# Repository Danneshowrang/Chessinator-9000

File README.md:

# Chessinator-9000
A smart open source folding chessboard. Future expansions planned with electromagnetic gantry.

# About
This board utilizes a network of hall sensors to track and log moves. Made up of 2 adjacent PCBs and designed to be foldable for improved portability. Future plans include a supplementary electromagnetic gantry and API connection to Lichess and Chess.com. Currently configured to project move and take a crowdvote for Open Sauce.

# Pictures

# CAD
Link to Onshape: https://cad.onshape.com/documents/2e4e2dec579cd54b02eea52a/w/9b3b1f51bd0c7211bdccebd8/e/a09db839a12e81c960572c26?renderMode=0&uiState=6a51f7b7bcb9fa1e94df709e

# Bill Of Materials

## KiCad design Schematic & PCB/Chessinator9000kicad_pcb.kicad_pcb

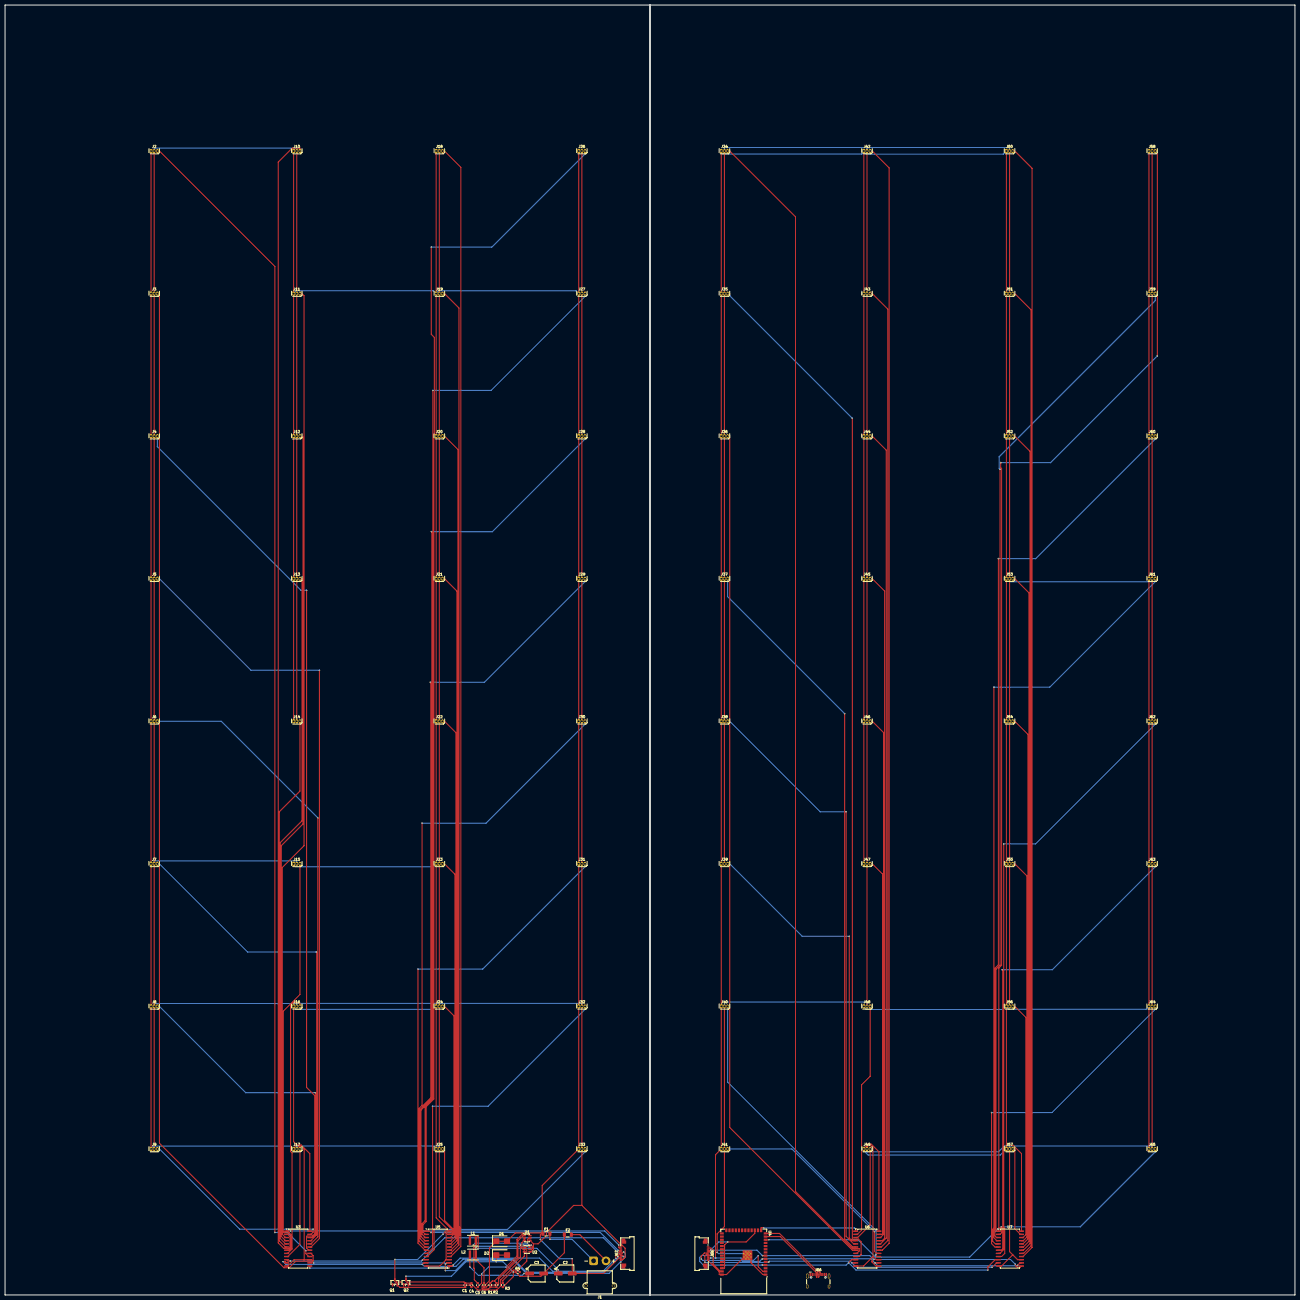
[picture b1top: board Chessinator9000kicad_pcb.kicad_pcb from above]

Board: 2 copper layers, 517.1 x 517.1 mm, 93 parts (0 on the bottom side), 91 nets.

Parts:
C1, C4, C5, C6: C; C_0603_1608Metric
C2, C3: C_Polarized; CP_Elec_6.3x5.4
D1, D2: D_TVS; D_SMB
F1, F2: Fuse; Fuse_1206_3216Metric
J1: Conn_01x02; AMASS_XT30PW-M_1x02_P2.50mm_Horizontal
J2, J3, J4, J5, J6, J7, J8, J9, J10, J11, J12, J13, J14, J15, J16, J17, J18, J19, J20, J21, J22, J23, J24, J25, J26, J27, J28, J29, J30, J31, J32, J33, J34, J35, J36, J37, J38, J39, J40, J41, J42, J43, J44, J45, J46, J47, J48, J49, J50, J51, J52, J53, J54, J55, J56, J57, J58, J59, J60, J61, J62, J63, J64, J65: Conn_01x03; TO-92S
J66: USB_C_Receptacle_USB2.0_16P; USB_C_Receptacle_HCTL_HC-TYPE-C-16P-01A
J67, J68: Conn_02x06_Odd_Even; Amphenol_F32Q-1A7x1-11012_1x12-1MP_P0.5mm_Horizontal
L1, L2: L; L_Coilcraft_XxL4020
Q1, Q2: PMOS; SOT-23
R1, R2, R3, R4: R; R_0603_1608Metric
U1: AP63203WU; TSOT-23-6
U2: AP63201WU; TSOT-23-6
U3, U5, U6, U7: CD74HC4067M; SOIC-24W_7.5x15.4mm_P1.27mm
U4: ESP32-S3-WROOM-1

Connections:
+3V3: C2.2, D1.1 (A1), D1.2 (A2), F1.1, J2.1 (VCC), J3.1 (VCC), J4.1 (VCC), J5.1 (VCC), J6.1 (VCC), J7.1 (VCC), J8.1 (VCC), J9.1 (VCC), J10.1 (VCC), J11.1 (VCC), J12.1 (VCC), J13.1 (VCC), J14.1 (VCC), J15.1 (VCC), J16.1 (VCC), J17.1 (VCC), J18.1 (VCC), J19.1 (VCC), J20.1 (VCC), J21.1 (VCC), J22.1 (VCC), J23.1 (VCC), J24.1 (VCC), J25.1 (VCC), J26.1 (VCC), J27.1 (VCC), J28.1 (VCC), J29.1 (VCC), J30.1 (VCC), J31.1 (VCC), J32.1 (VCC), J33.1 (VCC), J34.1 (VCC), J35.1 (VCC), J36.1 (VCC), J37.1 (VCC), J38.1 (VCC), J39.1 (VCC), J40.1 (VCC), J41.1 (VCC), J42.1 (VCC), J43.1 (VCC), J44.1 (VCC), J45.1 (VCC), J46.1 (VCC), J47.1 (VCC), J48.1 (VCC), J49.1 (VCC), J50.1 (VCC), J51.1 (VCC), J52.1 (VCC), J53.1 (VCC), J54.1 (VCC), J55.1 (VCC), J56.1 (VCC), J57.1 (VCC), J58.1 (VCC), J59.1 (VCC), J60.1 (VCC), J61.1 (VCC), J62.1 (VCC), J63.1 (VCC), J64.1 (VCC), J65.1 (VCC), J67.3, J67.4, J68.9, J68.10, Q1.3 (S), R1.1, R2.1, U3.24 (VCC), U4.2 (3V3), U5.24 (VCC), U6.24 (VCC), U7.24 (VCC)
+5V: C3.2, D2.1 (A1), D2.2 (A2), F2.1, Q2.3 (S), R3.1, R4.1
/Untitled Sheet/MUX3_COM: J67.9, J68.4, U4.17 (IO9), U4.38 (IO2), U5.1 (COM)
/Untitled Sheet/MUX4_COM: J67.10, J68.3
/Untitled Sheet/MUX_COM_EXTRA: J67.11, J68.2, U3.1 (COM), U4.39 (IO1)
/Untitled Sheet/MUX_S0: J67.5, J68.8, U3.10 (S0), U4.4 (IO4), U5.10 (S0), U6.10 (S0), U7.10 (S0)
/Untitled Sheet/MUX_S1: J67.6, J68.7, U3.11 (S1), U4.5 (IO5), U5.11 (S1), U6.11 (S1), U7.11 (S1)
/Untitled Sheet/MUX_S2: J67.7, J68.6, U3.14 (S2), U4.6 (IO6), U5.14 (S2), U6.14 (S2), U7.14 (S2)
/Untitled Sheet/MUX_S3: J67.8, J68.5, U3.13 (S3), U4.7 (IO7), U5.13 (S3), U6.13 (S3), U7.13 (S3)
GND: J2.2 (GND), J3.2 (GND), J4.2 (GND), J5.2 (GND), J6.2 (GND), J7.2 (GND), J8.2 (GND), J9.2 (GND), J10.2 (GND), J11.2 (GND), J12.2 (GND), J13.2 (GND), J14.2 (GND), J15.2 (GND), J16.2 (GND), J17.2 (GND), J18.2 (GND), J19.2 (GND), J20.2 (GND), J21.2 (GND), J22.2 (GND), J23.2 (GND), J24.2 (GND), J25.2 (GND), J26.2 (GND), J27.2 (GND), J28.2 (GND), J29.2 (GND), J30.2 (GND), J31.2 (GND), J32.2 (GND), J33.2 (GND), J34.2 (GND), J35.2 (GND), J36.2 (GND), J37.2 (GND), J38.2 (GND), J39.2 (GND), J40.2 (GND), J41.2 (GND), J42.2 (GND), J43.2 (GND), J44.2 (GND), J45.2 (GND), J46.2 (GND), J47.2 (GND), J48.2 (GND), J49.2 (GND), J50.2 (GND), J51.2 (GND), J52.2 (GND), J53.2 (GND), J54.2 (GND), J55.2 (GND), J56.2 (GND), J57.2 (GND), J58.2 (GND), J59.2 (GND), J60.2 (GND), J61.2 (GND), J62.2 (GND), J63.2 (GND), J64.2 (GND), J65.2 (GND), J67.1, J67.2, J68.11, J68.12, U1.4 (GND), U2.4 (GND), U3.12 (GND), U3.15 (~E), U4.1 (GND), U4.40 (GND), U4.41 (GND), U5.12 (GND), U5.15 (~E), U6.12 (GND), U6.15 (~E), U7.12 (GND), U7.15 (~E)
unnamed: C2.1, L1.1
unnamed: C3.1, L2.1
unnamed: F1.2, J1.1
unnamed: F2.2, J1.2
unnamed: J2.3 (PIT), U3.16 (I15)
unnamed: J3.3 (PIT), U3.17 (I14)
unnamed: J4.3 (PIT), U3.18 (I13)
unnamed: J5.3 (PIT), U3.19 (I12)
unnamed: J6.3 (PIT), U3.20 (I11)
unnamed: J7.3 (PIT), U3.21 (I10)
unnamed: J8.3 (PIT), U3.22 (I9)
unnamed: J9.3 (PIT), U3.23 (I8)
unnamed: J10.3 (PIT), U3.2 (I7)
unnamed: J11.3 (PIT), U3.3 (I6)
unnamed: J12.3 (PIT), U3.4 (I5)
unnamed: J13.3 (PIT), U3.5 (I4)
unnamed: J14.3 (PIT), U3.6 (I3)
unnamed: J15.3 (PIT), U3.7 (I2)
unnamed: J16.3 (PIT), U3.8 (I1)
unnamed: J17.3 (PIT), U3.9 (I0)
unnamed: J18.3 (PIT), U5.16 (I15)
unnamed: J19.3 (PIT), U5.17 (I14)
unnamed: J20.3 (PIT), U5.18 (I13)
unnamed: J21.3 (PIT), U5.19 (I12)
unnamed: J22.3 (PIT), U5.20 (I11)
unnamed: J23.3 (PIT), U5.21 (I10)
unnamed: J24.3 (PIT), U5.22 (I9)
unnamed: J25.3 (PIT), U5.23 (I8)
unnamed: J26.3 (PIT), U5.2 (I7)
unnamed: J27.3 (PIT), U5.3 (I6)
unnamed: J28.3 (PIT), U5.4 (I5)
unnamed: J29.3 (PIT), U5.5 (I4)
unnamed: J30.3 (PIT), U5.6 (I3)
unnamed: J31.3 (PIT), U5.7 (I2)
unnamed: J32.3 (PIT), U5.8 (I1)
unnamed: J33.3 (PIT), U5.9 (I0)
unnamed: J34.3 (PIT), U6.8 (I1)
unnamed: J35.3 (PIT), U6.9 (I0)
unnamed: J36.3 (PIT), U6.7 (I2)
unnamed: J37.3 (PIT), U6.6 (I3)
unnamed: J38.3 (PIT), U6.5 (I4)
unnamed: J39.3 (PIT), U6.4 (I5)
unnamed: J40.3 (PIT), U6.16 (I15)
unnamed: J41.3 (PIT), U6.17 (I14)
unnamed: J42.3 (PIT), U6.18 (I13)
unnamed: J43.3 (PIT), U6.19 (I12)
unnamed: J44.3 (PIT), U6.20 (I11)
unnamed: J45.3 (PIT), U6.21 (I10)
unnamed: J46.3 (PIT), U6.22 (I9)
unnamed: J47.3 (PIT), U6.23 (I8)
unnamed: J48.3 (PIT), U6.2 (I7)
unnamed: J49.3 (PIT), U6.3 (I6)
unnamed: J50.3 (PIT), U7.16 (I15)
unnamed: J51.3 (PIT), U7.17 (I14)
unnamed: J52.3 (PIT), U7.18 (I13)
unnamed: J53.3 (PIT), U7.19 (I12)
unnamed: J54.3 (PIT), U7.20 (I11)
unnamed: J55.3 (PIT), U7.21 (I10)
unnamed: J56.3 (PIT), U7.22 (I9)
unnamed: J57.3 (PIT), U7.23 (I8)
unnamed: J58.3 (PIT), U7.2 (I7)
unnamed: J59.3 (PIT), U7.3 (I6)
unnamed: J60.3 (PIT), U7.4 (I5)
unnamed: J61.3 (PIT), U7.5 (I4)
unnamed: J62.3 (PIT), U7.9 (I0)
unnamed: J63.3 (PIT), U7.8 (I1)
unnamed: J64.3 (PIT), U7.6 (I3)
unnamed: J65.3 (PIT), U7.7 (I2)
unnamed: C1.2, C4.2, Q1.1 (D), Q2.1 (D), U1.2 (EN), U1.3 (IN), U2.2 (EN), U2.3 (IN)
unnamed: C1.1, Q1.2 (G)
unnamed: C4.1, Q2.2 (G)
unnamed: C5.1, U1.6 (BST)
unnamed: R1.2, R2.2, U1.1 (FB)
unnamed: C5.2, L1.2, U1.5 (SW)
unnamed: C6.1, U2.6 (BST)
unnamed: R3.2, R4.2, U2.1 (FB)
unnamed: C6.2, L2.2, U2.5 (SW)
unnamed: U4.15 (IO3), U6.1 (COM)
unnamed: U4.12 (IO8), U7.1 (COM)
unnamed: J66.A6 (D+), J66.B6 (D+), U4.14 (USB_D+)
unnamed: J66.A7 (D-), J66.B7 (D-), U4.13 (USB_D-)

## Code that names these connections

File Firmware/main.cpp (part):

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#include <Adafruit_NeoPixel.h>

// ---------- Pin map (match schematic labels) ----------
constexpr uint8_t PIN_MUX_S0   = 4;
constexpr uint8_t PIN_MUX_S1   = 5;
constexpr uint8_t PIN_MUX_S2   = 6;
constexpr uint8_t PIN_MUX_S3   = 7;

constexpr uint8_t PIN_MUX1_COM = 1;   // IO1 - ADC
constexpr uint8_t PIN_MUX2_COM = 2;   // IO2 - ADC
constexpr uint8_t PIN_MUX3_COM = 38;  // IO38 - ADC (via J67/FFC)
constexpr uint8_t PIN_MUX4_COM = 39;  // IO39 - ADC (via J67/FFC)

constexpr uint8_t PIN_LED_DATA = 12;

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uint16_t hallRaw[NUM_MUX][NUM_CH];

const uint8_t muxCOMPins[NUM_MUX] = {
  PIN_MUX1_COM, PIN_MUX2_COM, PIN_MUX3_COM, PIN_MUX4_COM
};

// ---------- Forward declarations ----------
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void setup() {
  Serial.begin(115200);

  pinMode(PIN_MUX_S0, OUTPUT);
  pinMode(PIN_MUX_S1, OUTPUT);
  pinMode(PIN_MUX_S2, OUTPUT);
  pinMode(PIN_MUX_S3, OUTPUT);

  strip.begin();
  strip.show();
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// Mux control
// ---------------------------------------------------------------
void setMuxChannel(uint8_t ch) {
  digitalWrite(PIN_MUX_S0, ch & 0x01);
  digitalWrite(PIN_MUX_S1, (ch >> 1) & 0x01);
  digitalWrite(PIN_MUX_S2, (ch >> 2) & 0x01);
  digitalWrite(PIN_MUX_S3, (ch >> 3) & 0x01);
  delayMicroseconds(5); // settle time
}

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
